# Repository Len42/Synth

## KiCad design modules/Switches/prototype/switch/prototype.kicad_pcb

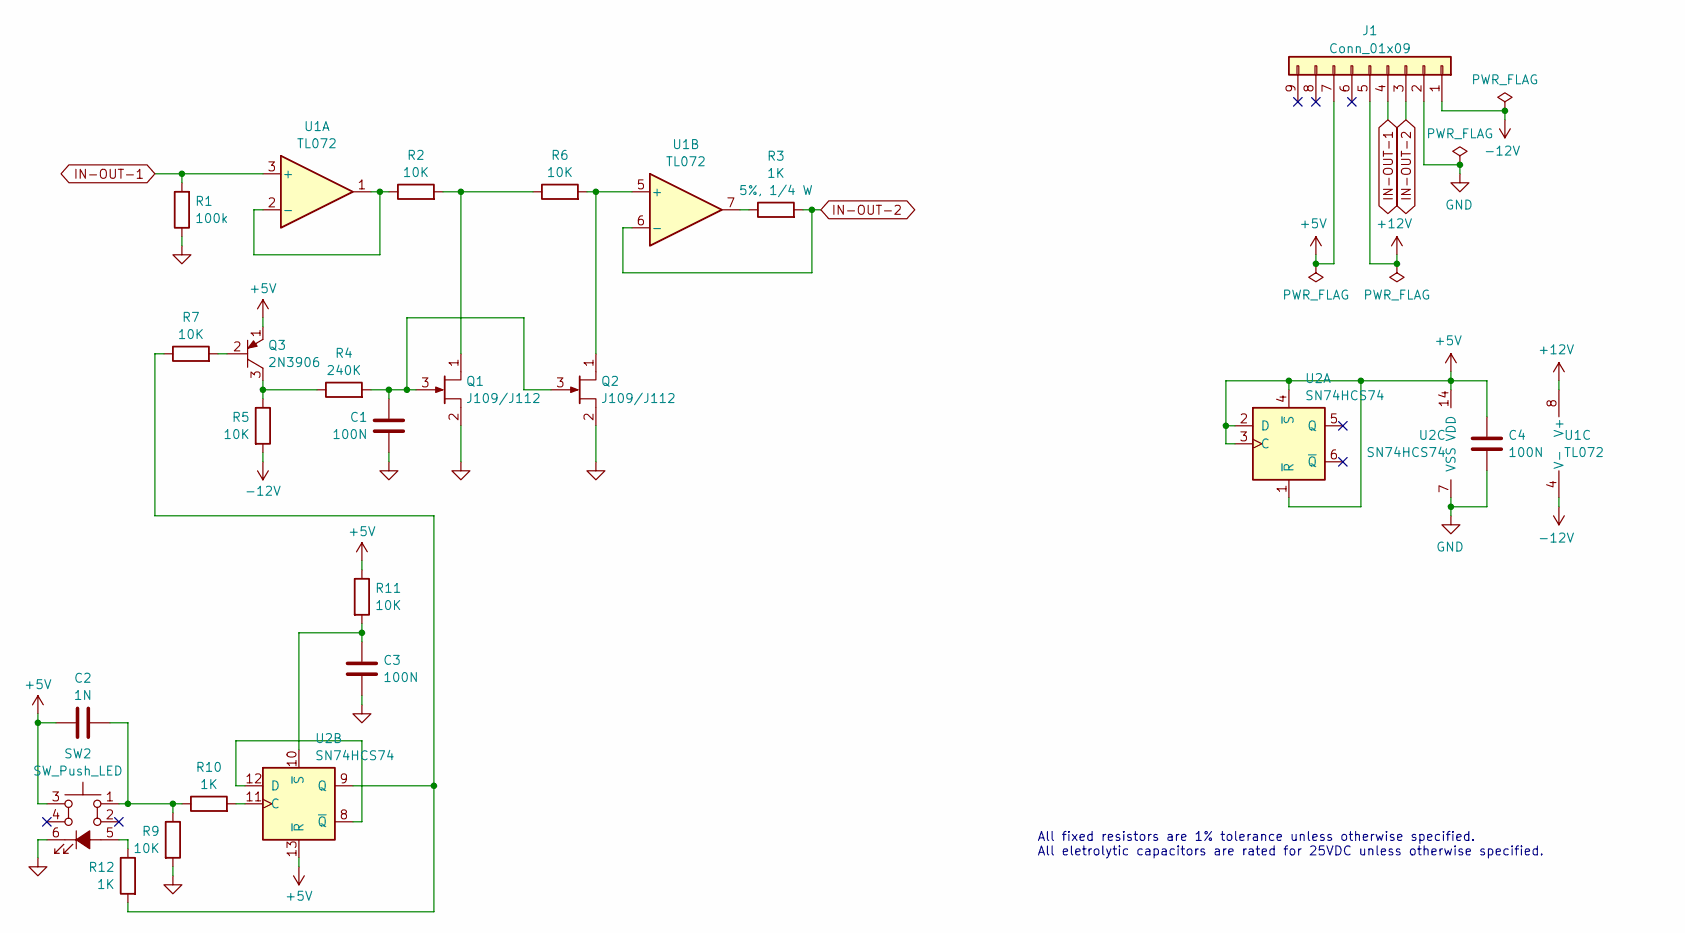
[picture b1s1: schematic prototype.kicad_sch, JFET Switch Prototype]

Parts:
C1, C3, C4: 100N; C_Disc_D5.0mm_W2.5mm_P2.50mm; ManufacturerPartNum FG18X7R1H104KNT06
C2: 1N; SB_Gen_2; ManufacturerPartNum FG18X7R1H104KNT06
J1: Conn_01x09; PinHeader_1x09_P2.54mm_Vertical
Q1, Q2: J109/J112; TO-92_Inline_Wide
Q3: 2N3906; TO-92_Inline_Wide; ManufacturerPartNum 2N3906TAR
R1: 100k; SB_Gen_1; ManufacturerPartNum MFR-12*
R2, R6, R11: 10K; R_Axial_DIN0207_L6.3mm_D2.5mm_P7.62mm_Horizontal; ManufacturerPartNum MFR-12*
R3: 1K; SB_Gen_2; ManufacturerPartNum CCF071K00JKE36
R4: 240K; SB_Gen_2; ManufacturerPartNum MFR-12*
R5, R7: 10K; SB_Gen_2; ManufacturerPartNum MFR-12*
R9: 10K; SB_Gen_1; ManufacturerPartNum MFR-12*
R10: 1K; SB_Gen_1; ManufacturerPartNum MFR-12*
R12: 1K; SB_Gen_1; ManufacturerPartNum CCF071K00JKE36
SW2: SW_Push_LED; SW_Push_LED_C&K_D6R; ManufacturerPartNum D6RLBUF1 LFS
U1: TL072; DIP-8_W7.62mm; ManufacturerPartNum TL072BCP
U2: SN74HCS74; Breakout_DIP-14_W15.24mm; ManufacturerPartNum SN74HCS74DR

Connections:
+5V: C2.1, C4.1, J1.7, Q3.1 (E), R11.1, SW2.3, U2.1 (~R), U2.2 (D), U2.3 (C), U2.4 (~S), U2.13 (~R), U2.14 (VDD)
+12V: J1.5, U1.8 (V+)
-12V: J1.1, R5.2, U1.4 (V-)
GND: C1.2, C3.2, C4.2, J1.2, Q1.2 (S), Q2.2 (S), R1.1, R9.2, SW2.6 (K), U2.7 (VSS)
IN-OUT-1: J1.4, R1.2, U1.3 (+)
IN-OUT-2: J1.3, R3.2, U1.6 (-)
unnamed: C2.2, R9.1, R10.1, SW2.1
unnamed: Q1.1 (D), R2.2, R6.1
unnamed: C1.1, Q1.3 (G), Q2.3 (G), R4.2
unnamed: Q2.1 (D), R6.2, U1.5 (+)
unnamed: Q3.2 (B), R7.2
unnamed: Q3.3 (C), R4.1, R5.1
unnamed: R3.1, U1.7
unnamed: R12.1, SW2.5 (A)
unnamed: R2.1, U1.1, U1.2 (-)
unnamed: R10.2, U2.11 (C)
unnamed: U2.8 (~Q), U2.12 (D)
unnamed: R7.1, R12.2, U2.9 (Q)
unnamed: C3.1, R11.2, U2.10 (~S)

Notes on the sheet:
All fixed resistors are 1% tolerance unless otherwise specified. All eletrolytic capacitors are rated for 25VDC unless otherwise specified.

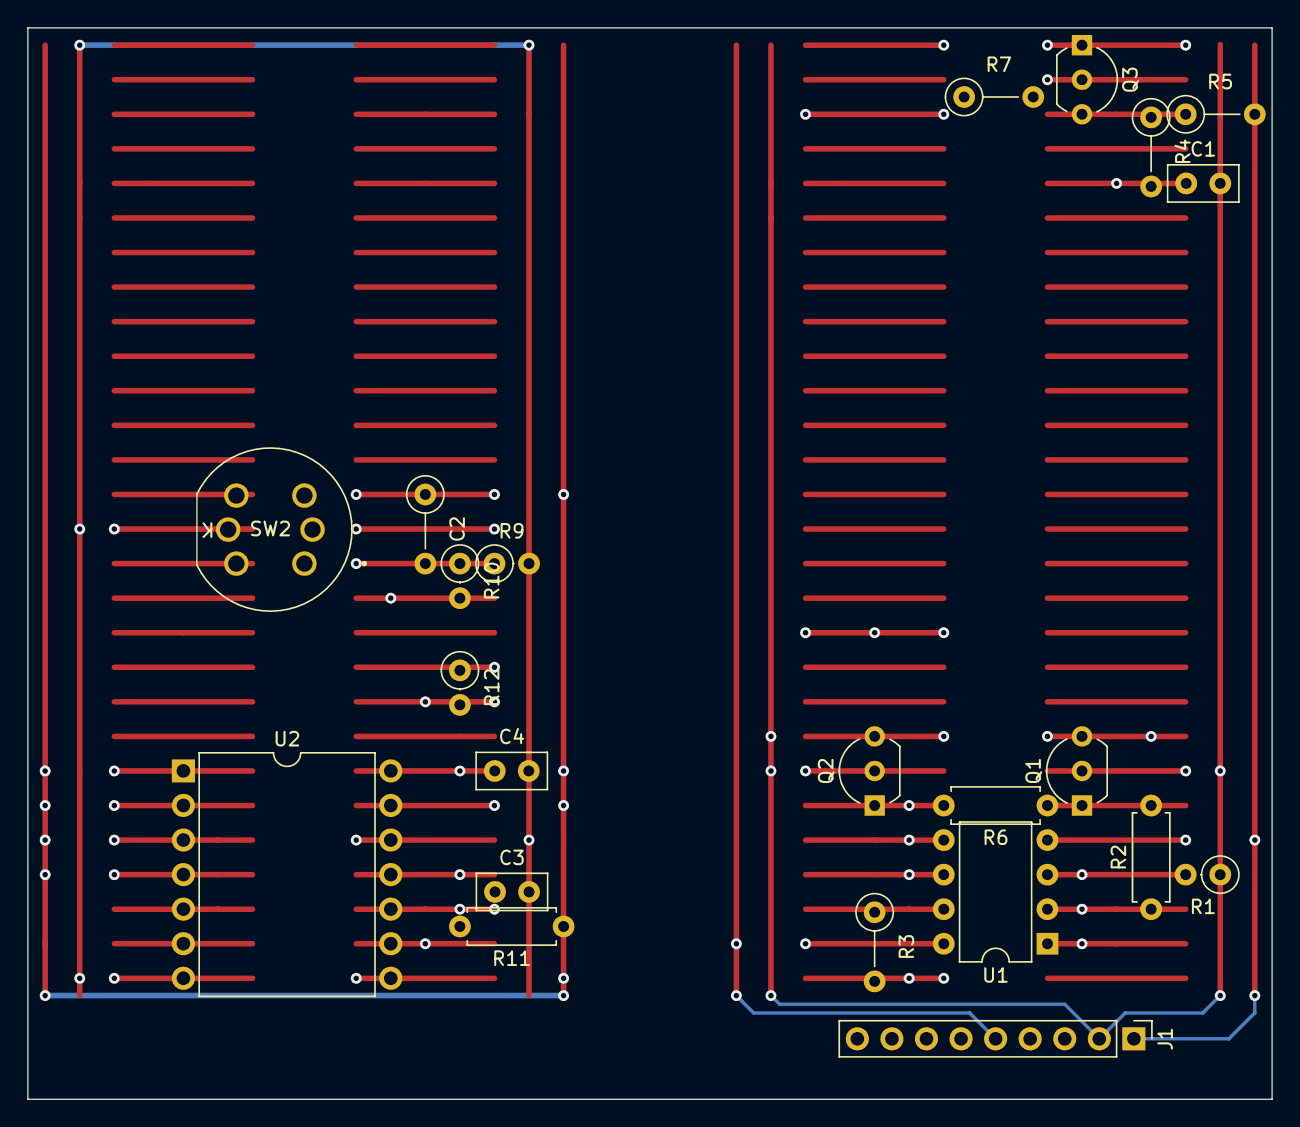
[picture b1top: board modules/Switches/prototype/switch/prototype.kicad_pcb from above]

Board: 6 copper layers, 91.4 x 78.7 mm, 22 parts (0 on the bottom side), 19 nets.

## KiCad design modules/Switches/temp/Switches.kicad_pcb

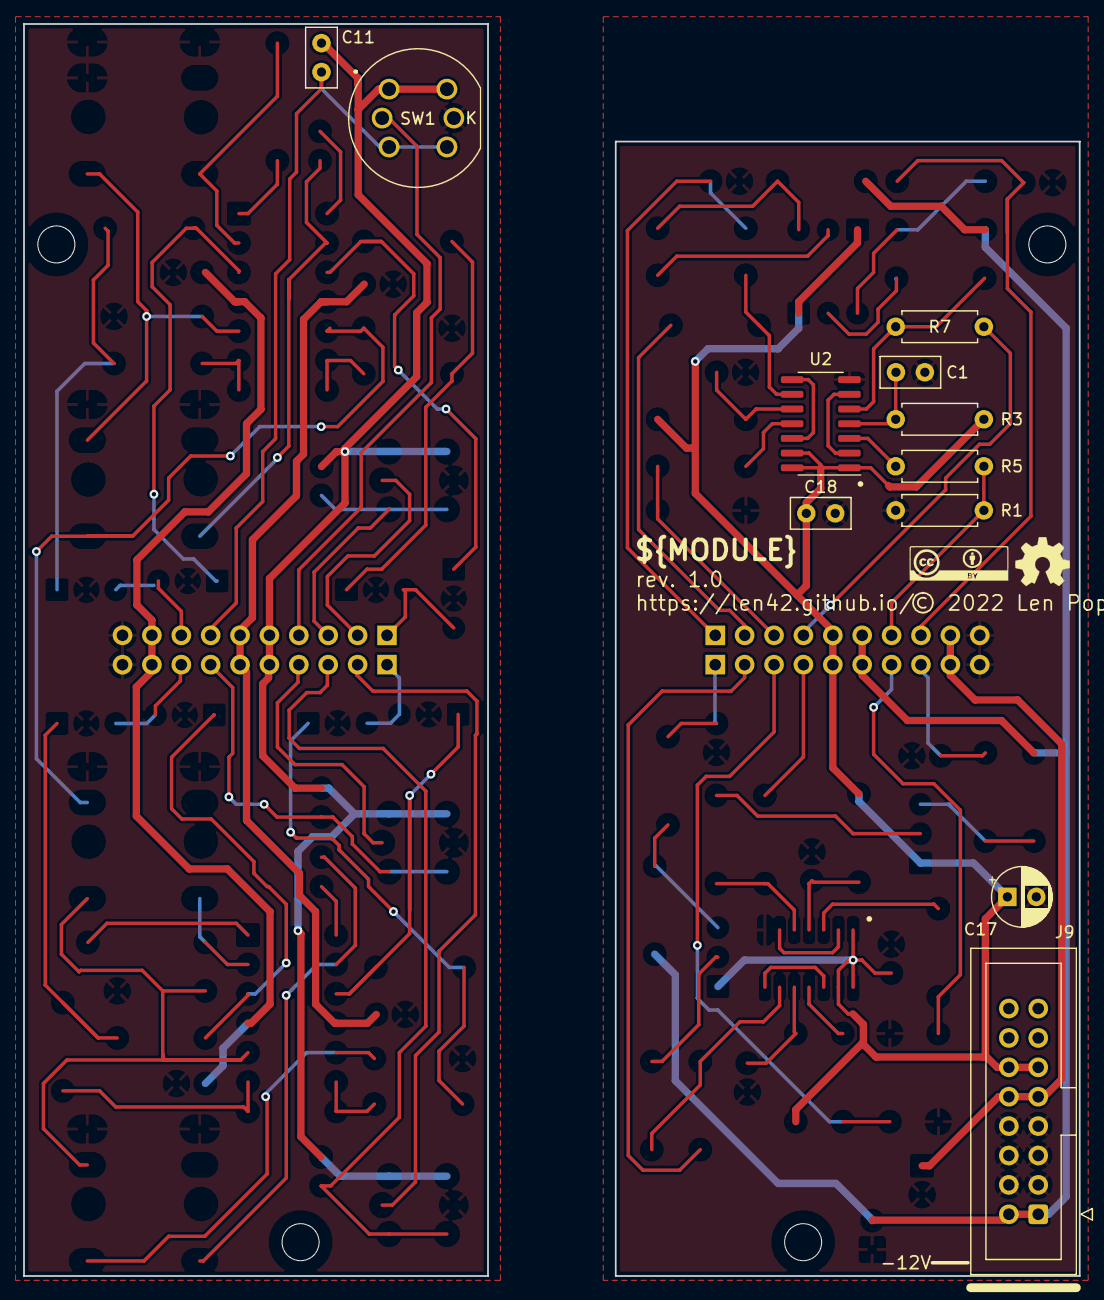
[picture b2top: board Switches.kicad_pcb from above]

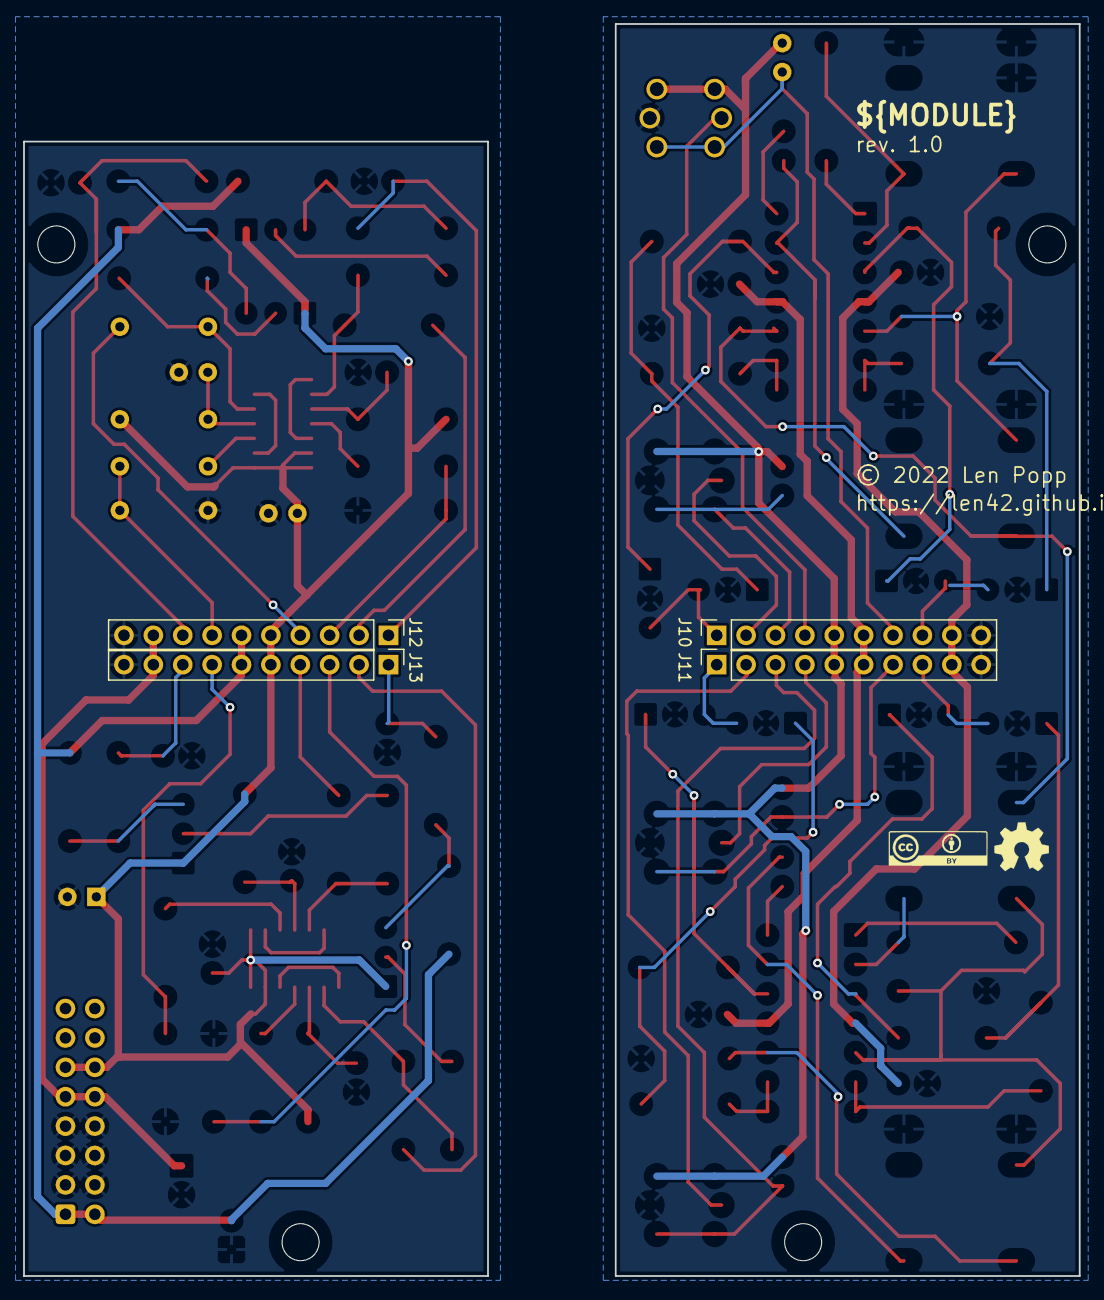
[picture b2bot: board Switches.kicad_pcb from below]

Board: 2 copper layers, 91.2 x 108.2 mm, 23 parts (6 on the bottom side), 20 nets.

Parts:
C1, C18: 100N; C_Disc_D5.0mm_W2.5mm_P2.50mm
C11: 1N; C_Disc_D5.0mm_W2.5mm_P2.50mm
C17: 10U; CP_Radial_D5.0mm_P2.50mm
G1, G6: Logo_CC_BY
G3, G5: Logo_OSHW
H2, H4, H7, H9: MountingHole_M3; MountingHole_PCB_3.2mm_M3
J9: Conn_Eurorack_16; IDC-Header-Eurorack-16-TH
J10: Conn_Front_Top; PinSocket_1x10_P2.54mm_Vertical
J11: Conn_Front_Bottom; PinSocket_1x10_P2.54mm_Vertical
J12: Conn_Back_Top; PinHeader_1x10_P2.54mm_Vertical
J13: Conn_Back_Bottom; PinHeader_1x10_P2.54mm_Vertical
R1, R3: 10K; R_Axial_DIN0207_L6.3mm_D2.5mm_P7.62mm_Horizontal
R5: 1K; R_Axial_DIN0207_L6.3mm_D2.5mm_P7.62mm_Horizontal
R7: 330R; R_Axial_DIN0207_L6.3mm_D2.5mm_P7.62mm_Horizontal
SW1: D6RLxxF1; SW_Push_LED_C&K_D6R
U2: SN74HCS74; SOIC-14_3.9x8.7mm_P1.27mm

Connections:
+5V: C11.1, C17.1, C18.1, J9.11 (+5V), J9.12, J10.5, J11.5, J12.5, J13.5, R3.1, SW1.1, SW1.2, U2.1 (~R), U2.14 (VDD)
+12V: J9.9 (+12V), J9.10, J10.9, J11.9, J12.9, J13.9
-12V: J9.1 (-12V), J9.2, J10.6, J11.6, J12.6, J13.6
GND: C1.2, C17.2, C18.2, J9.3 (GND), J9.4, J9.5 (GND), J9.6, J9.7 (GND), J9.8, J10.10, J11.10, J12.10, J13.10, R1.2, SW1.6 (K), U2.7 (VSS)
LED-1: J10.4, J12.4, R7.2, SW1.5 (A)
LED-2: J10.2, J12.2
LED-3: J11.4, J13.4
LED-4: J11.2, J13.2
MUTE-1: J10.8, J12.8
MUTE-2: J10.1, J12.1
MUTE-3: J11.8, J13.8
MUTE-4: J11.1, J13.1
unnamed: R5.2, U2.3 (C)
unnamed: U2.2 (D), U2.6 (~Q)
unnamed: R7.1, U2.5 (Q)
unnamed: C1.1, R3.2, U2.4 (~S)
SWITCH-1: C11.2, J10.7, J12.7, R1.1, R5.1, SW1.3, SW1.4
SWITCH-2: J10.3, J12.3
SWITCH-3: J11.7, J13.7
SWITCH-4: J11.3, J13.3

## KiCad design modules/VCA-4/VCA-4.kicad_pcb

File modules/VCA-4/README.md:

# Quad VCA

## 10HP Eurorack Module

### Features
- Four exponential VCAs based on an [SSI2164 chip](https://www.soundsemiconductor.com/downloads/ssi2164datasheet.pdf)
- Each VCA has a CV attenuator as well as a fixed-level control.
- Each CV input is normalled to the next one, so one CV can control multiple channels
- Each output is normalled to mix with the next channel's output

### Notes
PCB layouts are provided in KiCad and gerber formats. A front panel design is included as a drilled PCB layout (with no labels or graphics).

The PCBs that I used can be ordered from OSH Park. The designs are here:
- [Front panel](https://oshpark.com/shared_projects/qBEhyWJ7)
- [Controls board](https://oshpark.com/shared_projects/Fr2IHQ2I)
- [Middle board](https://oshpark.com/shared_projects/4RaINCLo)
- [Back board](https://oshpark.com/shared_projects/ozq05skM)

Please note that I am a hobbyist, not a trained electronics engineer. No guarantees!

### Software Used

[KiCad](https://www.kicad.org/) 6.0.4

<hr /><div><div style="float:left; padding-right:10px;"></div><div style="xfloat:left; padding-left:10px;"><br />© 2022 Len Popp CC BY<br />This work is licensed under a <a rel="license" href="http://creativecommons.org/licenses/by/4.0/">Creative Commons Attribution 4.0 International License</a>.</div></div>

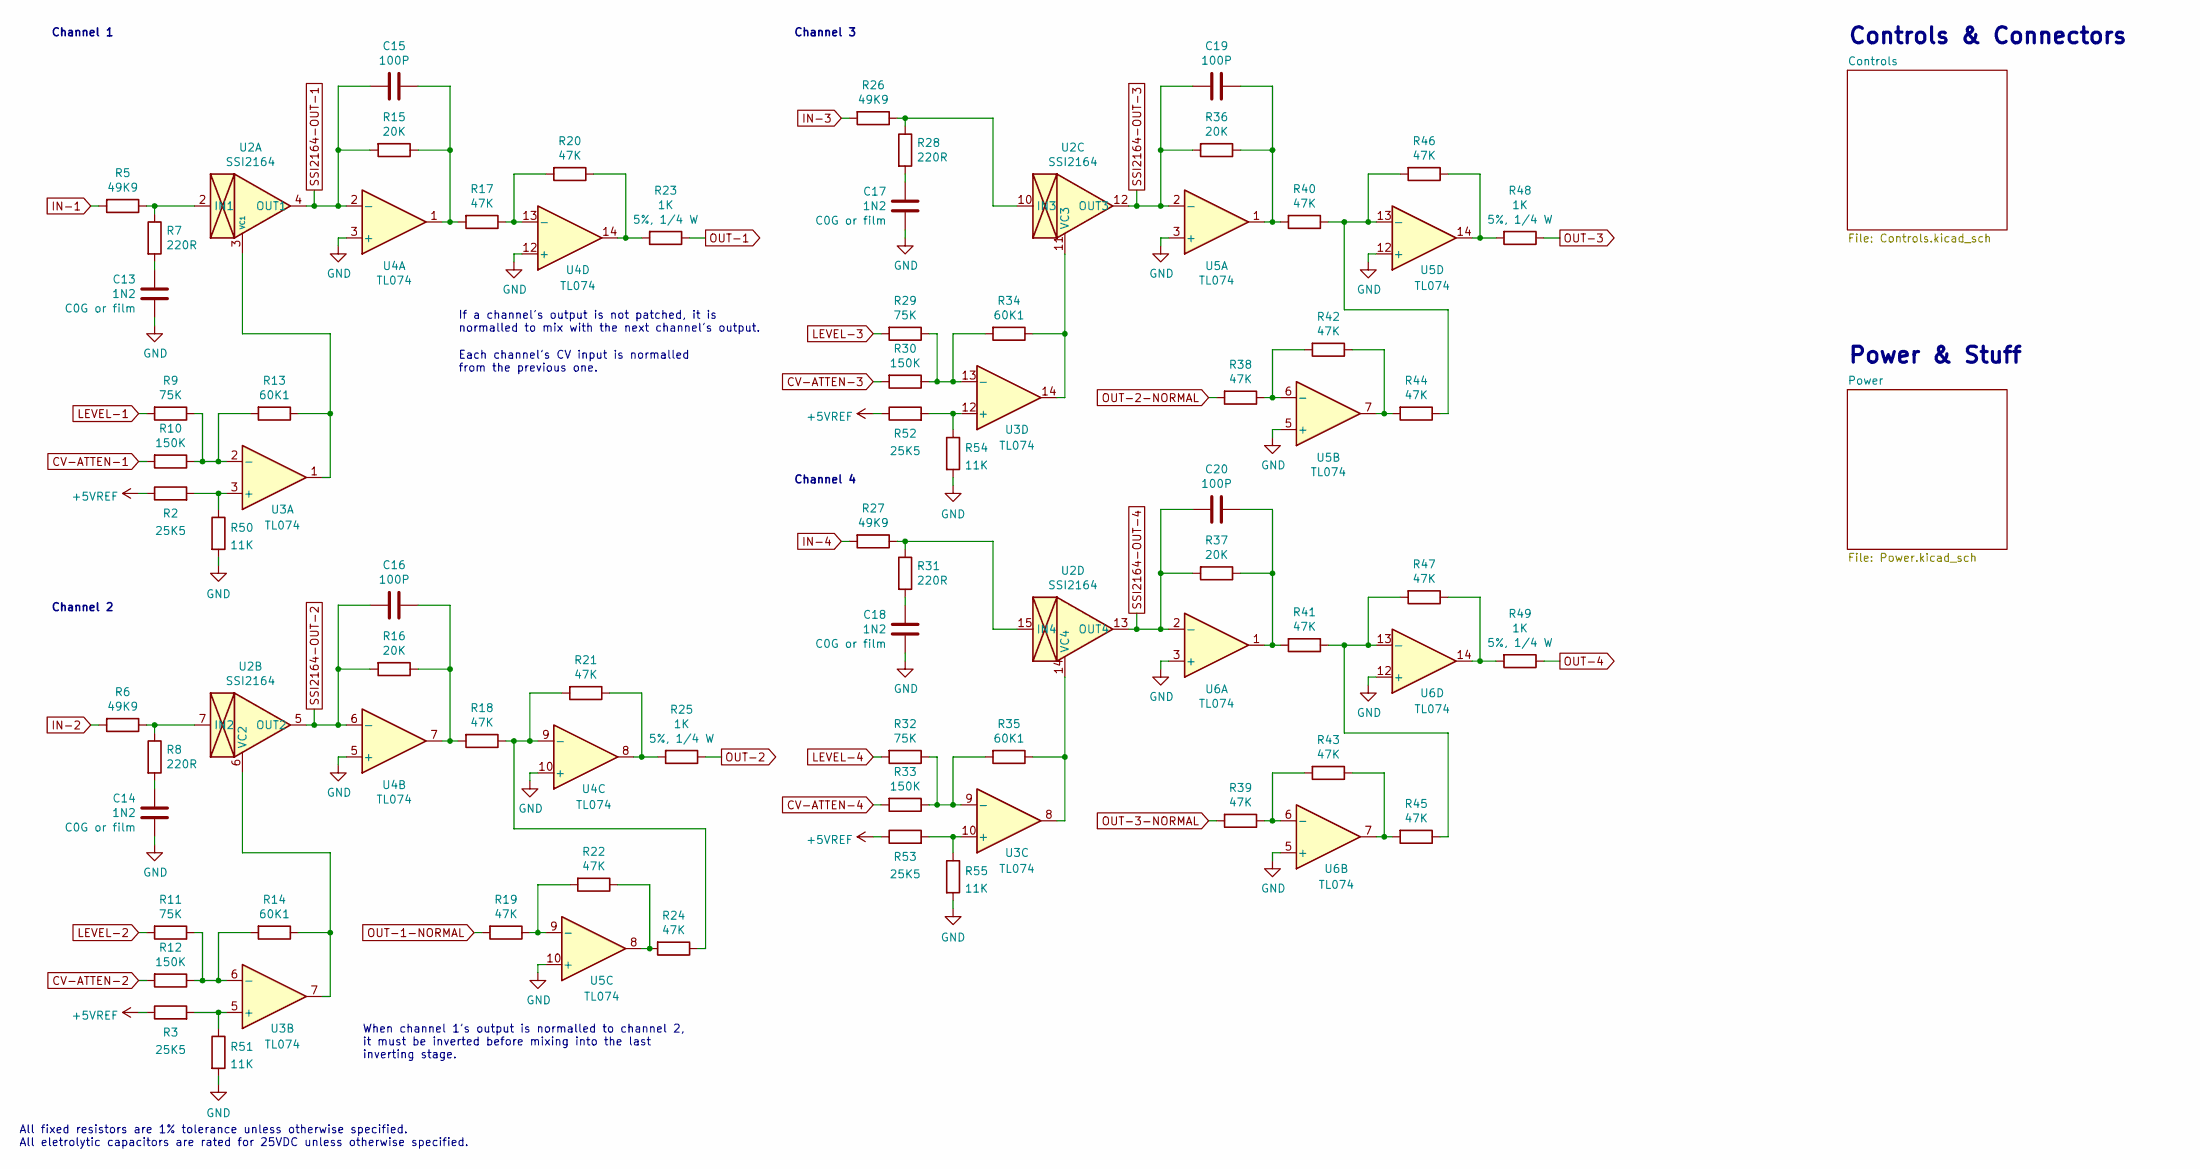
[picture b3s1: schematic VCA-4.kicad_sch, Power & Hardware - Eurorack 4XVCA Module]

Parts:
C13, C14, C17, C18: 1N2; C_Rect_Kemet_L7.2mm_W2.5mm_P5mm; ManufacturerPartNum R82EC1120DQ50J
C15, C16, C19, C20: 100P; C_Disc_D5.0mm_W2.5mm_P2.50mm; ManufacturerPartNum K101J15C0GF53L2
R2, R3, R52, R53: 25K5; R_Axial_DIN0207_L6.3mm_D2.5mm_P7.62mm_Horizontal; ManufacturerPartNum MFR-25FRF52-25K5
R5, R6, R26, R27: 49K9; R_Axial_DIN0207_L6.3mm_D2.5mm_P7.62mm_Horizontal; ManufacturerPartNum RN55D4992FB14
R7, R8, R28, R31: 220R; R_Axial_DIN0207_L6.3mm_D2.5mm_P7.62mm_Horizontal; ManufacturerPartNum MFR-12FTF52-220R
R9, R11, R29, R32: 75K; R_Axial_DIN0207_L6.3mm_D2.5mm_P7.62mm_Horizontal; ManufacturerPartNum MFR-12FTF52-75K
R10, R12, R30, R33: 150K; R_Axial_DIN0207_L6.3mm_D2.5mm_P7.62mm_Horizontal; ManufacturerPartNum MFR-12FTF52-150K
R13, R14, R34, R35: 60K1; R_Axial_DIN0207_L6.3mm_D2.5mm_P7.62mm_Horizontal; ManufacturerPartNum RN55D6012FB14
R15, R16, R36, R37: 20K; R_Axial_DIN0207_L6.3mm_D2.5mm_P7.62mm_Horizontal; ManufacturerPartNum MFR-12FTF52-20K
R17, R18, R19, R20, R21, R22, R24, R38, R39, R40, R41, R42, R43, R44, R45, R46, R47: 47K; R_Axial_DIN0207_L6.3mm_D2.5mm_P7.62mm_Horizontal; ManufacturerPartNum MFR-12FTF52-47K
R23, R25, R48, R49: 1K; R_Axial_DIN0207_L6.3mm_D2.5mm_P10.16mm_Horizontal; ManufacturerPartNum CCF071K00JKE36
R50, R51, R54, R55: 11K; R_Axial_DIN0207_L6.3mm_D2.5mm_P7.62mm_Horizontal; ManufacturerPartNum MFR-12FTF52-11K
U2: SSI2164; Breakout_DIP-SOIC-16_W15.24mm; ManufacturerPartNum SSI2164
U3, U4, U5, U6: TL074; DIP-14_W7.62mm; ManufacturerPartNum TL074BCN

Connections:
+5VREF: R2.1, R3.1, R52.1, R53.1; also elsewhere on the board
CV-ATTEN-1: R10.2; also elsewhere on the board
CV-ATTEN-2: R12.2; also elsewhere on the board
CV-ATTEN-3: R30.2; also elsewhere on the board
CV-ATTEN-4: R33.2; also elsewhere on the board
GND: C13.2, C14.2, C17.2, C18.2, R50.2, R51.2, R54.2, R55.2, U4.3 (+), U4.5 (+), U4.10 (+), U4.12 (+), U5.3 (+), U5.5 (+), U5.10 (+), U5.12 (+), U6.3 (+), U6.5 (+), U6.12 (+); also elsewhere on the board
IN-1: R5.2; also elsewhere on the board
IN-2: R6.2; also elsewhere on the board
IN-3: R26.2; also elsewhere on the board
IN-4: R27.2; also elsewhere on the board
LEVEL-1: R9.2; also elsewhere on the board
LEVEL-2: R11.2; also elsewhere on the board
LEVEL-3: R29.2; also elsewhere on the board
LEVEL-4: R32.2; also elsewhere on the board
unnamed: C13.1, R7.2
unnamed: C14.1, R8.2
unnamed: C15.1, R15.1, R17.2, U4.1
unnamed: C16.1, R16.1, R18.2, U4.7
unnamed: C17.1, R28.2
unnamed: C18.1, R31.2
unnamed: C19.1, R36.1, R40.2, U5.1
unnamed: C20.1, R37.1, R41.2, U6.1
unnamed: R2.2, R50.1, U3.3 (+)
unnamed: R3.2, R51.1, U3.5 (+)
unnamed: R5.1, R7.1, U2.2 (IN1)
unnamed: R6.1, R8.1, U2.7 (IN2)
unnamed: R9.1, R10.1, R13.2, U3.2 (-)
unnamed: R11.1, R12.1, R14.2, U3.6 (-)
unnamed: R13.1, U2.3 (VC1), U3.1
unnamed: R14.1, U2.6 (VC2), U3.7
unnamed: R17.1, R20.2, U4.13 (-)
unnamed: R18.1, R21.2, R24.1, U4.9 (-)
unnamed: R19.1, R22.2, U5.9 (-)
unnamed: R20.1, R23.2, U4.14
unnamed: R21.1, R25.2, U4.8
unnamed: R22.1, R24.2, U5.8
unnamed: R26.1, R28.1, U2.10 (IN3)
unnamed: R27.1, R31.1, U2.15 (IN4)
unnamed: R29.1, R30.1, R34.2, U3.13 (-)
unnamed: R32.1, R33.1, R35.2, U3.9 (-)
unnamed: R34.1, U2.11 (VC3), U3.14
unnamed: R35.1, U2.14 (VC4), U3.8
unnamed: R38.1, R42.2, U5.6 (-)
unnamed: R39.1, R43.2, U6.6 (-)
unnamed: R40.1, R44.1, R46.2, U5.13 (-)
unnamed: R41.1, R45.1, R47.2, U6.13 (-)
unnamed: R42.1, R44.2, U5.7
unnamed: R43.1, R45.2, U6.7
unnamed: R46.1, R48.2, U5.14
unnamed: R47.1, R49.2, U6.14
unnamed: R52.2, R54.1, U3.12 (+)
unnamed: R53.2, R55.1, U3.10 (+)
OUT-1: R23.1; also elsewhere on the board
OUT-1-NORMAL: R19.2; also elsewhere on the board
OUT-2: R25.1; also elsewhere on the board
OUT-2-NORMAL: R38.2; also elsewhere on the board
OUT-3: R48.1; also elsewhere on the board
OUT-3-NORMAL: R39.2; also elsewhere on the board
OUT-4: R49.1; also elsewhere on the board
SSI2164-OUT-1: C15.2, R15.2, U2.4 (OUT1), U4.2 (-); also elsewhere on the board
SSI2164-OUT-2: C16.2, R16.2, U2.5 (OUT2), U4.6 (-); also elsewhere on the board
SSI2164-OUT-3: C19.2, R36.2, U2.12 (OUT3), U5.2 (-); also elsewhere on the board
SSI2164-OUT-4: C20.2, R37.2, U2.13 (OUT4), U6.2 (-); also elsewhere on the board

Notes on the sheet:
When channel 1's output is normalled to channel 2, it must be inverted before mixing into the last inverting stage.
Power & Stuff
All fixed resistors are 1% tolerance unless otherwise specified. All eletrolytic capacitors are rated for 25VDC unless otherwise specified.
Channel 2
Channel 3
Channel 4
Controls & Connectors
Each channel's CV input is normalled from the previous one.
Channel 1
If a channel's output is not patched, it is normalled to mix with the next channel's output.

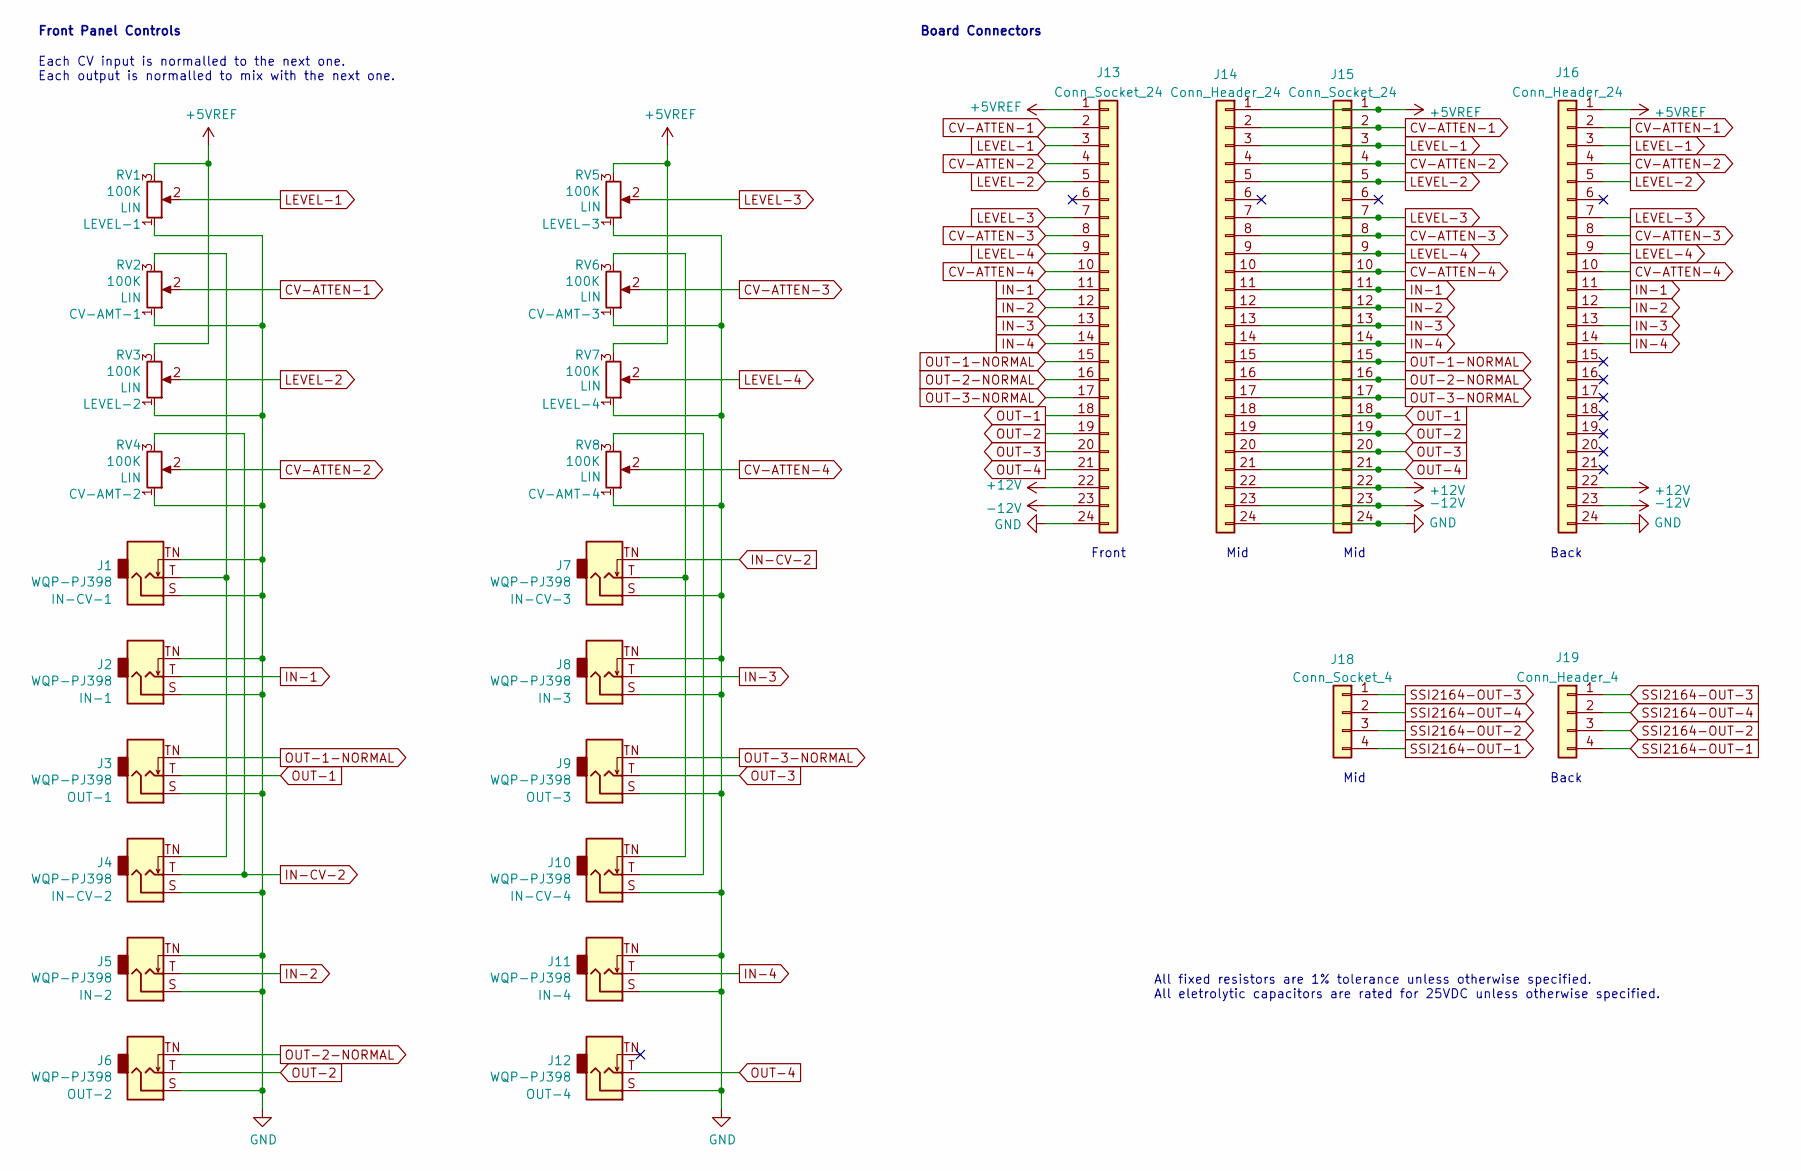
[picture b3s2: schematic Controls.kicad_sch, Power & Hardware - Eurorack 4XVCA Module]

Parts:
J1, J2, J3, J4, J5, J6, J7, J8, J9, J10, J11, J12: WQP-PJ398; Jack_3.5mm_QingPu_WQP-PJ398SM_Vertical; ManufacturerPartNum PJ398SM / WQP518MA
J13, J15: Conn_Socket_24; PinSocket_1x24_P2.54mm_Vertical
J14, J16: Conn_Header_24; PinHeader_1x24_P2.54mm_Vertical
J18: Conn_Socket_4; PinSocket_1x04_P2.54mm_Vertical
J19: Conn_Header_4; PinHeader_1x04_P2.54mm_Vertical
RV1, RV3, RV5, RV7: 100K; Potentiometer_Alpha_RD901F-40-00D_Single_Vertical; ManufacturerPartNum RD901F-40-15R1-B100K-00DL1
RV2, RV4, RV6, RV8: 100K; Potentiometer_SongHuei_Single_Vertical; ManufacturerPartNum R0904N*

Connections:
+5VREF: J13.1, J14.1, J15.1, J16.1, RV1.3, RV3.3, RV5.3, RV7.3; also elsewhere on the board
+12V: J13.22, J14.22, J15.22, J16.22; also elsewhere on the board
-12V: J13.23, J14.23, J15.23, J16.23; also elsewhere on the board
CV-ATTEN-1: J13.2, J14.2, J15.2, J16.2, RV2.2; also elsewhere on the board
CV-ATTEN-2: J13.4, J14.4, J15.4, J16.4, RV4.2; also elsewhere on the board
CV-ATTEN-3: J13.8, J14.8, J15.8, J16.8, RV6.2; also elsewhere on the board
CV-ATTEN-4: J13.10, J14.10, J15.10, J16.10, RV8.2; also elsewhere on the board
GND: J1.S, J1.TN, J2.S, J2.TN, J3.S, J4.S, J5.S, J5.TN, J6.S, J7.S, J8.S, J8.TN, J9.S, J10.S, J11.S, J11.TN, J12.S, J13.24, J14.24, J15.24, J16.24, RV1.1, RV2.1, RV3.1, RV4.1, RV5.1, RV6.1, RV7.1, RV8.1; also elsewhere on the board
IN-1: J2.T, J13.11, J14.11, J15.11, J16.11; also elsewhere on the board
IN-2: J5.T, J13.12, J14.12, J15.12, J16.12; also elsewhere on the board
IN-3: J8.T, J13.13, J14.13, J15.13, J16.13; also elsewhere on the board
IN-4: J11.T, J13.14, J14.14, J15.14, J16.14; also elsewhere on the board
IN-CV-2: J4.T, J7.TN, RV4.3
LEVEL-1: J13.3, J14.3, J15.3, J16.3, RV1.2; also elsewhere on the board
LEVEL-2: J13.5, J14.5, J15.5, J16.5, RV3.2; also elsewhere on the board
LEVEL-3: J13.7, J14.7, J15.7, J16.7, RV5.2; also elsewhere on the board
LEVEL-4: J13.9, J14.9, J15.9, J16.9, RV7.2; also elsewhere on the board
unnamed: J1.T, J4.TN, RV2.3
unnamed: J10.T, RV8.3
unnamed: J7.T, J10.TN, RV6.3
OUT-1: J3.T, J13.18, J14.18, J15.18; also elsewhere on the board
OUT-1-NORMAL: J3.TN, J13.15, J14.15, J15.15; also elsewhere on the board
OUT-2: J6.T, J13.19, J14.19, J15.19; also elsewhere on the board
OUT-2-NORMAL: J6.TN, J13.16, J14.16, J15.16; also elsewhere on the board
OUT-3: J9.T, J13.20, J14.20, J15.20; also elsewhere on the board
OUT-3-NORMAL: J9.TN, J13.17, J14.17, J15.17; also elsewhere on the board
OUT-4: J12.T, J13.21, J14.21, J15.21; also elsewhere on the board
SSI2164-OUT-1: J18.4, J19.4; also elsewhere on the board
SSI2164-OUT-2: J18.3, J19.3; also elsewhere on the board
SSI2164-OUT-3: J18.1, J19.1; also elsewhere on the board
SSI2164-OUT-4: J18.2, J19.2; also elsewhere on the board

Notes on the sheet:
All fixed resistors are 1% tolerance unless otherwise specified. All eletrolytic capacitors are rated for 25VDC unless otherwise specified.
Back
Mid
Board Connectors
Each CV input is normalled to the next one. Each output is normalled to mix with the next one.
Front
Front Panel Controls

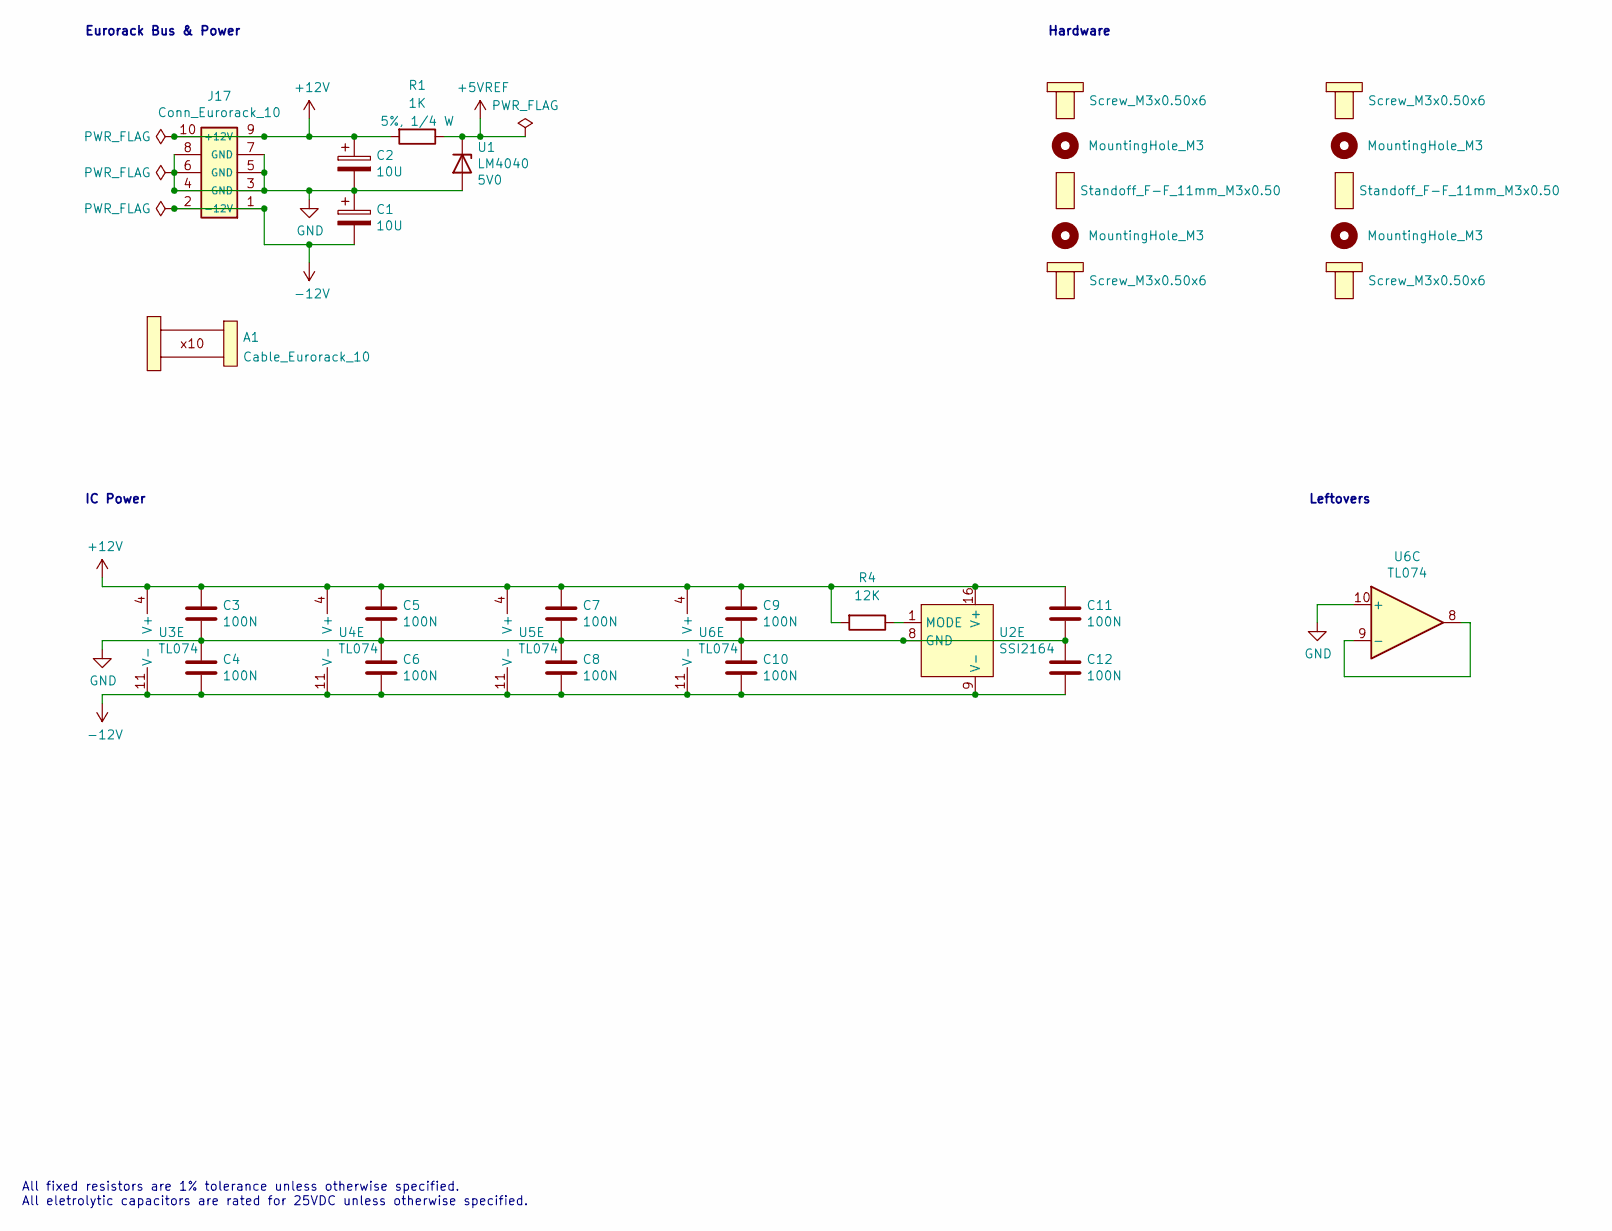
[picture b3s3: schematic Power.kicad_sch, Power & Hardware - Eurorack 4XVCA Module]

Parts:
A1: Cable_Eurorack_10; NoFootprint
C1, C2: 10U; CP_Radial_D4.0mm_P1.50mm; ManufacturerPartNum EEA-FC1E100
C3, C4, C5, C6, C7, C8, C9, C10, C11, C12: 100N; C_Disc_D5.0mm_W2.5mm_P2.50mm; ManufacturerPartNum FG18X7R1H104KNT06
H1, H5, H6, H10: Screw_M3x0.50x6
H2, H4, H7, H9: MountingHole_M3; MountingHole_PCB_3.2mm_M3
H3, H8: Standoff_F-F_11mm_M3x0.50; ManufacturerPartNum 05.03.111
J17: Conn_Eurorack_10; IDC-Header-Eurorack-10-TH; ManufacturerPartNum 61201021621
R1: 1K; R_Axial_DIN0207_L6.3mm_D2.5mm_P10.16mm_Horizontal; ManufacturerPartNum CCF071K00JKE36
R4: 12K; R_Axial_DIN0207_L6.3mm_D2.5mm_P7.62mm_Horizontal; ManufacturerPartNum MFR-12FTF52-12K
U1: LM4040; TO-92-2_Wide; ManufacturerPartNum LM4040BIZ-5.0/NOPB
U2: SSI2164; Breakout_DIP-SOIC-16_W15.24mm; ManufacturerPartNum SSI2164
U3, U4, U5, U6: TL074; DIP-14_W7.62mm; ManufacturerPartNum TL074BCN

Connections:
+5VREF: R1.1, U1.1 (K); also elsewhere on the board
+12V: C2.1, C3.1, C5.1, C7.1, C9.1, C11.1, J17.9 (+12V), J17.10, R1.2, R4.2, U2.16 (V+), U3.4 (V+), U4.4 (V+), U5.4 (V+), U6.4 (V+); also elsewhere on the board
-12V: C1.2, C4.2, C6.2, C8.2, C10.2, C12.2, J17.1 (-12V), J17.2, U2.9 (V-), U3.11 (V-), U4.11 (V-), U5.11 (V-), U6.11 (V-); also elsewhere on the board
GND: C1.1, C2.2, C3.2, C4.1, C5.2, C6.1, C7.2, C8.1, C9.2, C10.1, C11.2, C12.1, J17.3 (GND), J17.4, J17.5 (GND), J17.6, J17.7 (GND), J17.8, U1.2 (A), U2.8 (GND), U6.10 (+); also elsewhere on the board
unnamed: R4.1, U2.1 (MODE)
unnamed: U6.8, U6.9 (-)

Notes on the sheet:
IC Power
Leftovers
Eurorack Bus & Power
All fixed resistors are 1% tolerance unless otherwise specified. All eletrolytic capacitors are rated for 25VDC unless otherwise specified.
Hardware

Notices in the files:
modules/Switches/prototype/fake-vactrol/prototype.kicad_sch:
Copyright © 2023 Len Popp CC BY
modules/VCA-4/Controls.kicad_sch:
Copyright © 2021 Len Popp CC BY
modules/VCF-4P/VCF-4P.kicad_pcb:
Copyright © 2022 Len Popp CC BY
